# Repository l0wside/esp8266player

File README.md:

esp8266player - Kindgerechte Steuerung für einen Raumfeld One S
===============================================================

Motivation
----------
Der Player ist inspiriert von der [Toniebox](https://tonies.de/). Wer´s nicht kennt: das Kind hat ein Gerät, darauf stellt es eine Figur (die eine RFID-Kennung enthält), das Gerät lädt sich vom Server die zughörige Audiodatei und spielt los. Kein Gefummel mit CDs, die sowieso immer zerkratzen.

Nachteile an diesem System: man ist auf die Firma angewiesen, ohne Tonies keine Toniebox. Ohne Login geht nichts. Und: alle vorhandenen CDs (und bei uns sind das eine Menge) taugen nur noch als Frisbee oder Briefbeschwerer, eigene Inhalte lassen sich nur schwer wiedergeben.

Umsetzung
---------
Mit der Soft- und Hardware in diesem Projekt lässt sich ein Raumfeld One S per RFID fernsteuern. Dazu wird die sog. URI, die einen Track eindeutig bezeichnet, auf der Mifare-Karte gespeichert. Wird diese Karte dann auf den Player gelegt, sendet diese die URI an den Raumfeld One S, der diese URi dann abspielt. 
Vorteil: alles, was man mit der Raumfeld-App abspielen kann, lässt sich auch auf der Karte speichern. Theoretisch jedenfalls, ich habe es nur mit gerippten CDs auf dem NAS getestet.

Die Bedienung ist maximal simpel: Karte auflegen, ein paar Sekunden warten, Raumfeld dudelt los.

Programmiert werden die Karten ganz einfach: mit der Raumfeld-App einen Track auswählen. Wenn er spielt, auf den Player eine leere Mifare 1k-Karte legen. Der Player erkennt diese und schreibt die URI des aktuellen Tracks darauf. 

Wird die Karte nun wieder aufgelegt, wird der Track als neue URI an den Raumfeld gesendet, und dieser beginnt zu spielen. Wird die Karte weggenommen, wird ein Stop-Befehl an den Raumfeld gesendet.
Alle 20s wird die aktuelle Tracknummer abgefragt und (bei Änderung) auf der Karte gespeichert, so dass, wenn die Karte erneut aufgelegt wird, die CD nicht wieder von vorne losläuft. Was passiert, wenn ein Radiosender oder Spotify eingestellt ist, ist nicht getestet.

Bei uns sind statt RFID-Karten Aufkleber im Einsatz, die auf Holzwürfel geklebt werden. Irgendwann beschrifte ich die noch mit dem Laser.

Sonos und Co
------------
Implementiert ist ganz normales UPnP, das vermutlich mit einer Änderung des initialen Ports (bei Raumfeld 47365) auch mit Sonos läuft. Mangels Sonos habe ich es aber nicht getestet, ich freue mich auf Pull Requests.

Software
--------
Ein erster Umsetzungsversuch mit MicroPython scheiterte am komplett unbenutzbaren Netwerkstack von uPy auf ESP8266. Jetzt basiert die Software auf Arduino. Für RFID nutze ich die Lib von Miguel Balboa, der Zugriff auf den Raumfeld (SOAP über HTTP) ist selbst implementiert.

Hardware
--------
Basis ist ein ESP8266 (ESP13) auf dem im Repository enthaltenen Board. Achtung: der Schaltregler auf dem Board funktioniert zwar prinzipiell, bräuchte aber eine Spule, die größer ist, als der Platz erlaubt. Eine Vorgängerversion hatte mal einen LP3874-3.3 (Linearregler) eingebaut, der funktionierte erheblich besser.
Für Lauter, Leiser, Vor, Zurück sind insgesamt vier Touchfelder vorhanden, die mit Azoteq IQS127D ausgewertet werden. Wer sich das nicht traut, kann auch normale Taster nehmen, muss aber dafür sorgen, dass die Bootkonfiguration weiterhin funktioniert.
Für RFID kommt ein Chinaboard mit RC522 zum Einsatz, wie sie für rund 5 EUR z.B. bei eBay zu bekommen sind.

To Do
-----
* Hardware
  * Nicht funktionierenden Schaltregler sanieren oder durch Linearregler ersetzen
  * Einspeisung über Micro-USB-Buchse statt fest verlöteten Anschluss
  * Die Pinreihenfolge beim Anschluss des RFID-Boards müsste umgedreht werden, dann lässt sich 1:1 verbinden
  * Alternativ: RC522 direkt auf dem Board bestücken und Antenne integrieren.
* Software
  * Ist der Raumfeld im Standby, wird er nicht geweckt. 
  * Gelegentlich funktioniert die Erkennung der RFID-Karten nach einer Weile nicht mehr.
  * Als Status-LED wäre eine WS2812 prima, die dann farblich anzeigen könnte, wie es dem Gerät geht (suche WLAN, suche Raumfeld, Raumfeld gefunden, Karte im Feld, Raumfeld spielt). Das aktuelle Geblinke der blauen LED ist eher nervig.
  * Lauter/Leiser funktioniert nur mittelprächtig (in der App ist das viel besser). Wahrscheinlich wäre es sinnvoll, dafür eine permanent offene HTTP-Verbindung zu halten (also nicht Connection: close, sondern Connection: keep-alive) und mit inkrementellen statt absoluten Lautstärkebefehlen zu arbeiten.

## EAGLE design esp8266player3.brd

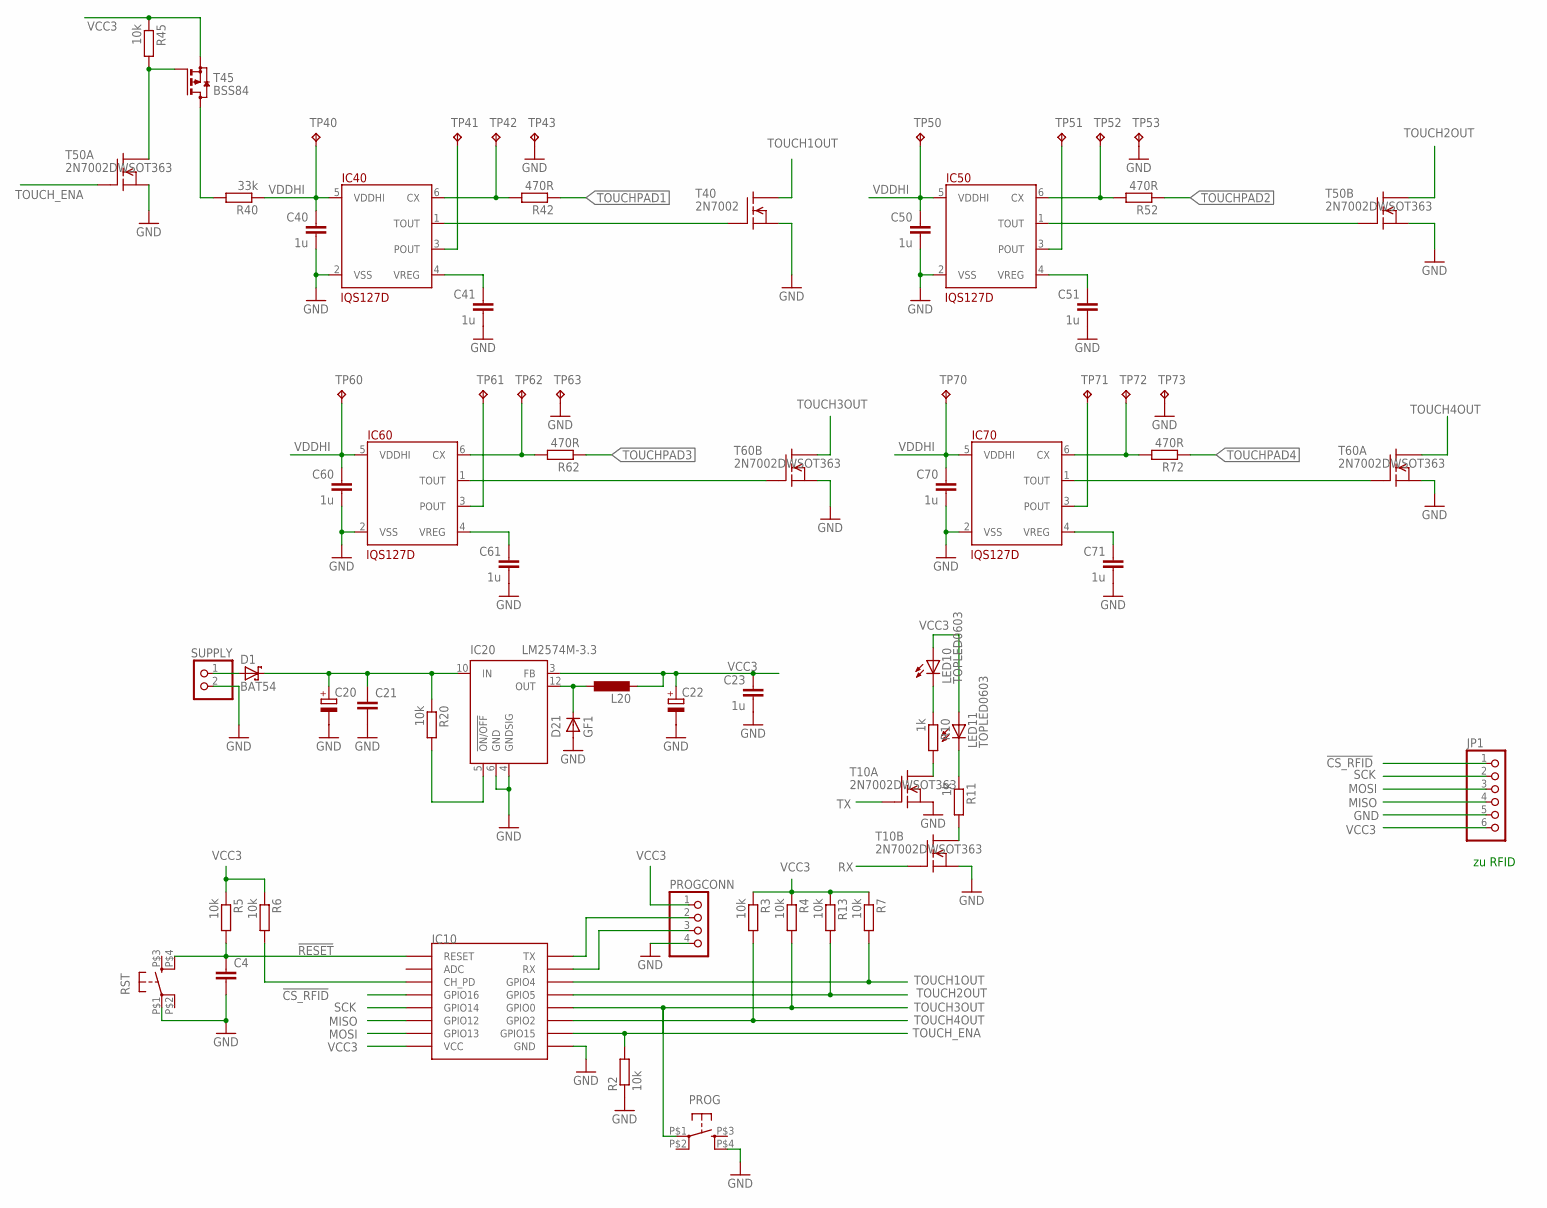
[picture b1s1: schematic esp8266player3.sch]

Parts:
C4: C-EUC0603; C0603
C20: CPOL-EUC; PANASONIC_C
C21: C-EUC1206; C1206
C22: CPOL-EUF; PANASONIC_F
C23, C40, C41, C50, C51, C60, C61, C70, C71: 1u; C0603
D1: BAT54; SOT23
D21: GF1; SMA-DO214AC
IC10: ESP12SMD; ESP12-SMD
IC20: LM2574M-3.3; SO14W
IC40, IC50, IC60, IC70: IQS127D; SOT23-6
JP1: PINHD-1X6; 1X06
L20: L-EUSRR0603; SRR6603-BOURNS
LED10, LED11: TOPLED0603; LED-0603-OSRAM
PROG: 10-XXTL3305; TL3305
PROGCONN: PINHD-1X4; 1X04
R2, R3, R4, R5, R6, R7, R13, R20, R45: 10k; R0603@1
R10, R11: 1k; R0603@1
R40: 33k; R0603@1
R42, R52, R62, R72: 470R; R0603@1
RST: 10-XXTL3305; TL3305
SUPPLY: PINHD-1X2; 1X02
T10, T50, T60: 2N7002DWSOT363; SOT363
T40: 2N7002; SOT23
T45: BSS84; SOT23
TP40, TP41, TP42, TP43, TP50, TP51, TP52, TP53, TP60, TP61, TP62, TP63, TP70, TP71, TP72, TP73: TPB1,27; B1,27

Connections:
!CS_RFID: IC10.GPIO16, JP1.1
!RESET: C4.1, IC10.RESET, R5.2, RST.P$4 (S1)
GND: C4.2, C20.-, C21.2, C22.-, C23.2, C40.2, C41.2, C50.2, C51.2, C60.2, C61.2, C70.2, C71.2, D21.A, IC10.GND, IC20.4 (GNDSIG), IC20.6 (GND), IC40.2 (VSS), IC50.2 (VSS), IC60.2 (VSS), IC70.2 (VSS), JP1.5, PROG.P$4 (S1), PROGCONN.4, R2.1, RST.P$1, SUPPLY.2, T10.1 (S), T10.4 (S), T40.2 (S), T50.1 (S), T50.4 (S), T60.1 (S), T60.4 (S), TP43.TP, TP53.TP, TP63.TP, TP73.TP
MISO: IC10.GPIO12, JP1.4
MOSI: IC10.GPIO13, JP1.3
unnamed: IC20.5 (!ON/OFF), R20.2
unnamed: D1.1 (A), SUPPLY.1
unnamed: R11.2, T10.6 (D)
unnamed: LED11.K@1 (C), R11.1
unnamed: D21.K (C), IC20.12 (OUT), L20.1
unnamed: LED10.K@1 (C), R10.1
unnamed: R10.2, T10.3 (D)
unnamed: IC10.CH_PD, R6.2
POUT_PROT1: IC60.3 (POUT), TP61.TP
POUT_PROT2: IC40.3 (POUT), TP41.TP
POUT_PROT3: IC70.3 (POUT), TP71.TP
POUT_PROT4: IC50.3 (POUT), TP51.TP
RX: IC10.RXD0 (RX), PROGCONN.3, T10.2 (G)
SCK: IC10.GPIO14, JP1.2
TOUCH1: IC40.1 (TOUT), T40.1 (G)
TOUCH1OUT: IC10.GPIO4, R7.2, T40.3 (D)
TOUCH2: IC50.1 (TOUT), T50.2 (G)
TOUCH2OUT: IC10.GPIO5, R13.2, T50.6 (D)
TOUCH3: IC60.1 (TOUT), T60.2 (G)
TOUCH3OUT: IC10.GPIO0, PROG.P$1, R4.2, T60.6 (D)
TOUCH4: IC70.1 (TOUT), T60.5 (G)
TOUCH4OUT: IC10.GPIO2, R3.2, T60.3 (D)
TOUCHPAD1: R42.1
TOUCHPAD2: R52.1
TOUCHPAD3: R62.1
TOUCHPAD4: R72.1
TOUCH_ENA: IC10.GPIO15, R2.2, T50.5 (G)
TOUCH_ENA2: R45.2, T45.1 (G), T50.3 (D)
TT: IC60.6 (CX), R62.2, TP62.TP
TT1: IC40.6 (CX), R42.2, TP42.TP
TT2: IC70.6 (CX), R72.2, TP72.TP
TT3: IC50.6 (CX), R52.2, TP52.TP
TX: IC10.TXD0 (TX), PROGCONN.2, T10.5 (G)
VCC3: C22.+, C23.1, IC10.VCC, IC20.3 (FB), JP1.6, L20.2, LED10.A@1 (A), LED11.A@1 (A), PROGCONN.1, R3.1, R4.1, R5.1, R6.1, R7.1, R13.1, R45.1, T45.2 (S)
VCC3_TOUCH: R40.2, T45.3 (D)
VDDHI: C40.1, C50.1, C60.1, C70.1, IC40.5 (VDDHI), IC50.5 (VDDHI), IC60.5 (VDDHI), IC70.5 (VDDHI), R40.1, TP40.TP, TP50.TP, TP60.TP, TP70.TP
VIN: C20.+, C21.1, D1.3 (C), IC20.10 (IN), R20.1
VREG1: C61.1, IC60.4 (VREG)
VREG2: C41.1, IC40.4 (VREG)
VREG3: C71.1, IC70.4 (VREG)
VREG4: C51.1, IC50.4 (VREG)

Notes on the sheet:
zu RFID

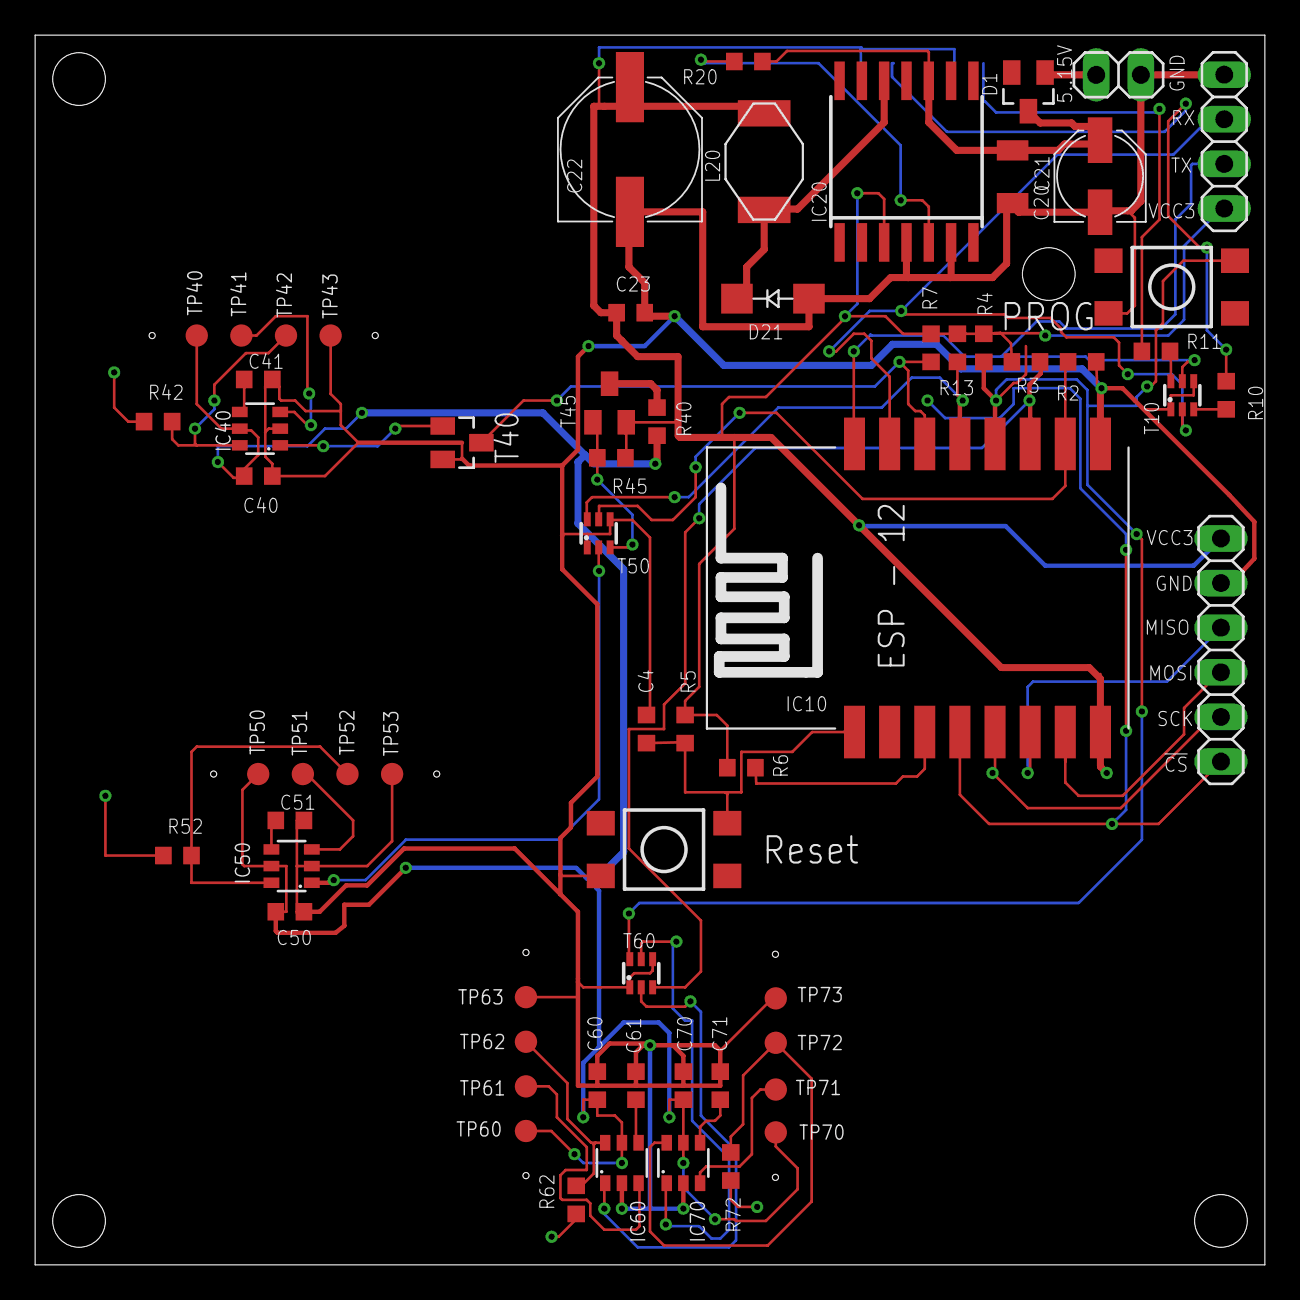
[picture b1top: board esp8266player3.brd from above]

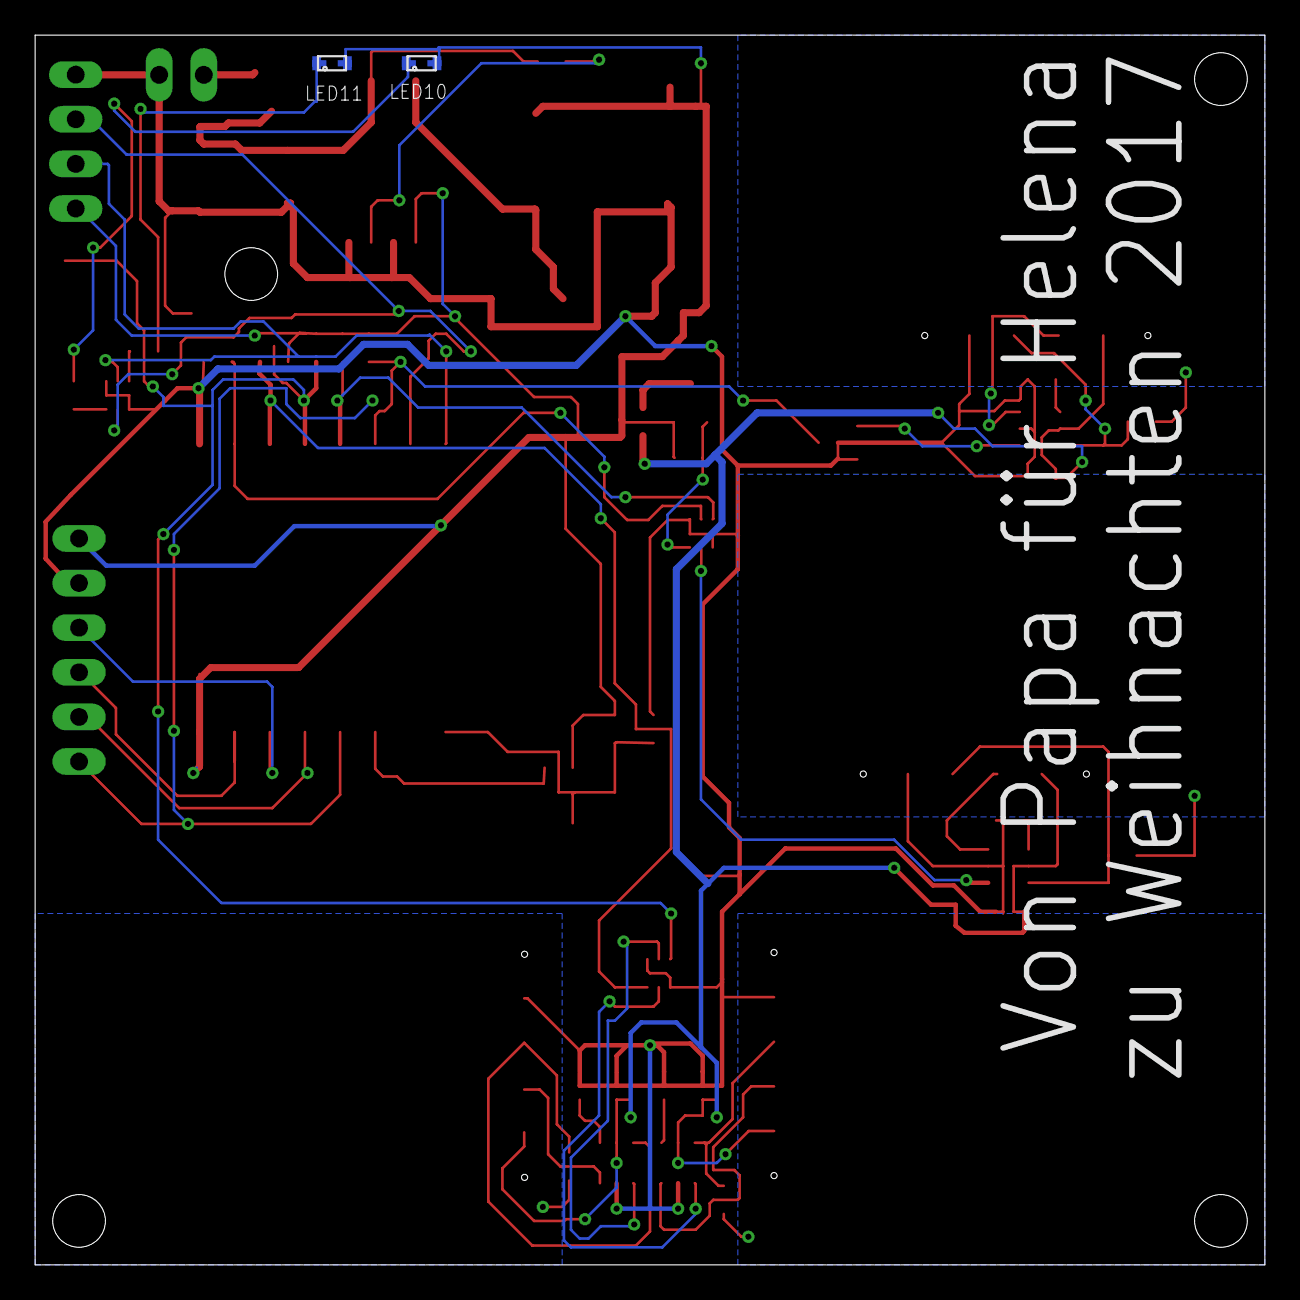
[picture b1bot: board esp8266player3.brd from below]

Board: 2 copper layers, 70.0 x 70.0 mm, 66 parts (2 on the bottom side), 42 nets.
